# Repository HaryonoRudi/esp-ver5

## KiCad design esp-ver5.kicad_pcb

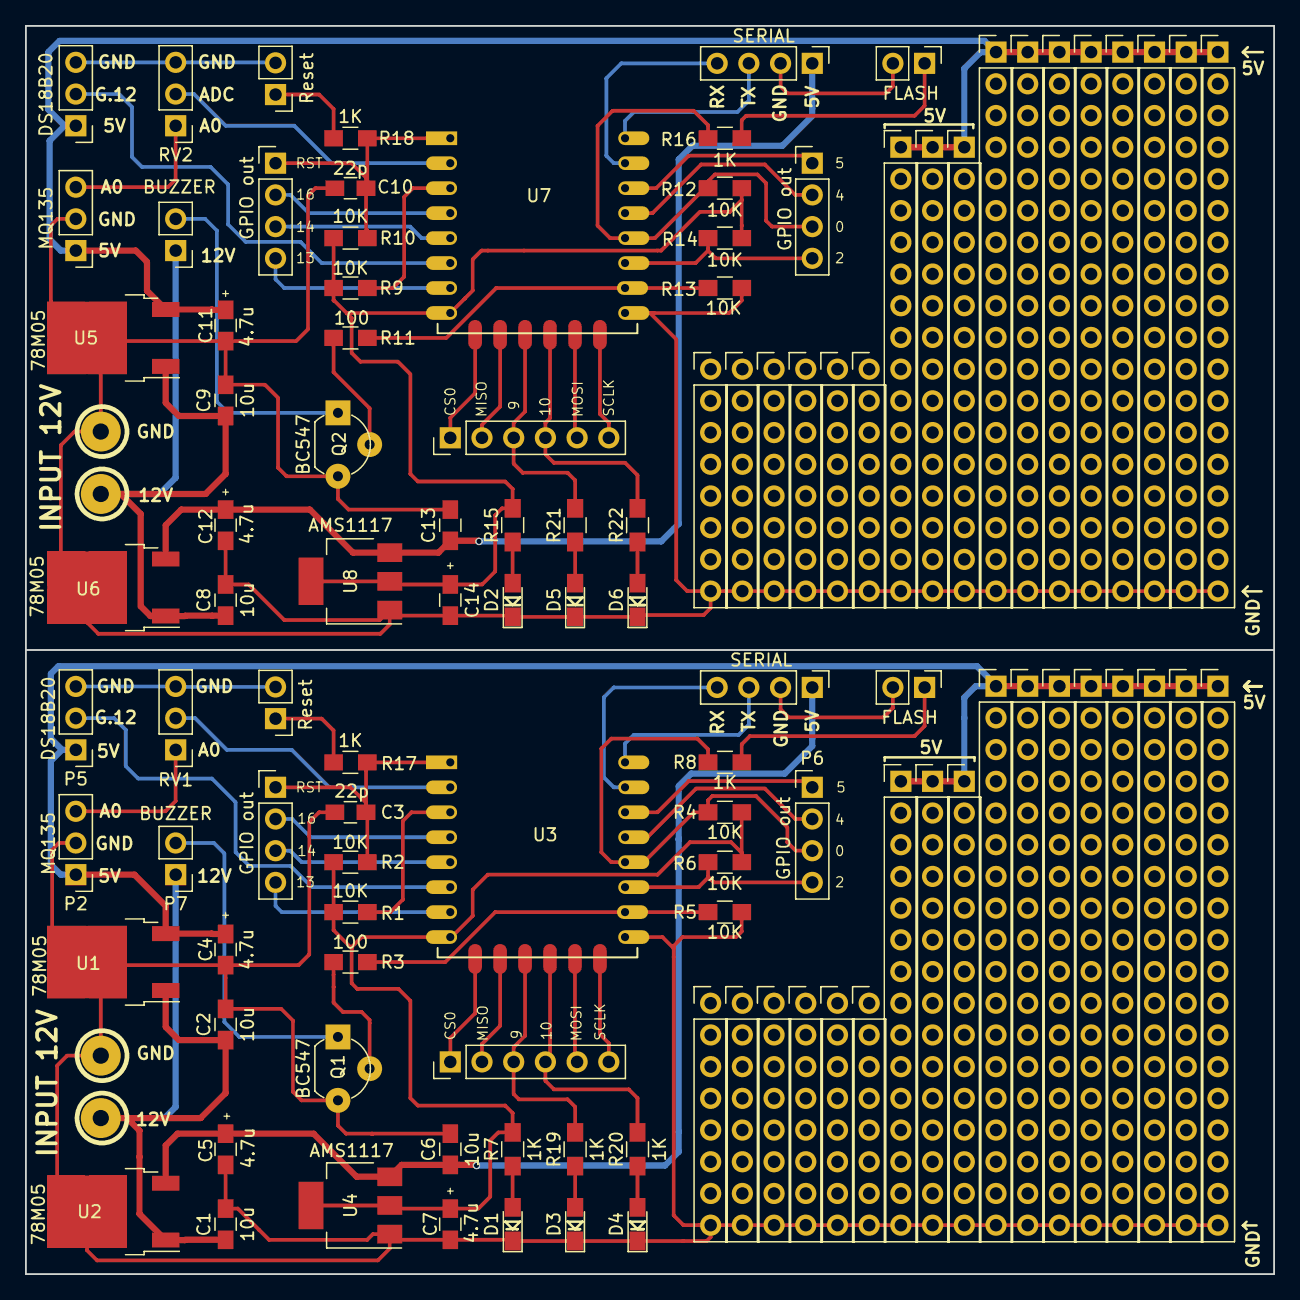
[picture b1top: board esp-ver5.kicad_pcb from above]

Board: 2 copper layers, 100.0 x 100.0 mm, 108 parts (0 on the bottom side), 65 nets.

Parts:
C1, C2, C6, C8, C9, C13: 10u; C_0805_HandSoldering
C3, C10: 22p; C_0805_HandSoldering
C4, C5, C7, C11, C12, C14: 4.7u; C_0805_HandSoldering
D1, D2, D3, D4, D5, D6: LED; LED_0805_HandSoldering
JP1, JP2: FLASH; Pin_Header_Straight_1x02_Pitch2.54mm
JP3, JP4: Reset; Pin_Header_Straight_1x02_Pitch2.54mm
P1, P8: INPUT 12V; mkds_1,5-2
P2, P9: MQ135; Pin_Header_Straight_1x03_Pitch2.54mm
P3, P10: SERIAL; Pin_Header_Straight_1x04_Pitch2.54mm
P4, P6, P13, P14: GPIO out; Pin_Header_Straight_1x04_Pitch2.54mm
P5, P11: DS18B20; Pin_Header_Straight_1x03_Pitch2.54mm
P7, P12: BUZZER; Pin_Header_Straight_1x02_Pitch2.54mm
P15, P16: GPIO out; Pin_Header_Straight_1x06_Pitch2.54mm
P17, P19, P21, P23, P24, P25, P28, P29, P34, P36, P38, P40, P43, P46, P49, P50: P; Pin_Header_Straight_1x18_Pitch2.54mm
P18, P20, P22, P35, P37, P39: P; Pin_Header_Straight_1x15_Pitch2.54mm
P26, P27, P30, P31, P32, P33, P41, P42, P44, P45, P47, P48: P; Pin_Header_Straight_1x08_Pitch2.54mm
Q1, Q2: BC547; TO-92_Molded_Wide
R1, R2, R4, R5, R6, R9, R10, R12, R13, R14: 10K; R_0805_HandSoldering
R3, R11: 100; R_0805_HandSoldering
R7, R8, R15, R16, R17, R18, R19, R20, R21, R22: 1K; R_0805_HandSoldering
RV1, RV2: 10K; Pin_Header_Straight_1x03_Pitch2.54mm
U1, U2, U5, U6: 78M05; TO-252-2
U3, U7: ESP-12E
U4, U8: AMS1117; SOT-223-3Lead_TabPin2

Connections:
3.3v: C14.1, R9.1, R10.2, R12.2, R14.2, R15.2, U7.8, U8.2
3V3: C7.1, R1.1, R2.2, R4.2, R6.2, R7.2, U3.8, U4.2
5.0v: C12.1, C13.1, P10.1, U6.3, U8.3
5V: C5.1, C6.1, P3.1, U2.3, U4.3
12V: C1.1, C2.1, P1.1, P7.1, U1.1, U2.1
A0: P2.3, RV1.1
ADC: RV1.2, U3.2
CS0: P15.1, U3.17
EN: R1.2, U3.3
G0: P14.3, R12.1, R16.1, U7.12
G2: P14.4, R14.1, U7.11
G4: P14.2, U7.13
G5: P14.1, U7.14
G9: P16.3, R21.2, U7.19
G10: P16.4, R22.2, U7.20
G12: P11.2, U7.6
G13: P13.4, U7.7
G14: P13.3, U7.5
G15: R11.2, R13.2, U7.10
G16: P13.2, U7.4
GND: C1.2, C2.2, C3.1, C4.2, C5.2, C6.2, C7.2, C8.2, C9.2, C10.1, C11.2, C12.2, C13.2, C14.2, D1.1, D2.1, D3.1, D4.1, D5.1, D6.1, JP1.2, JP2.2, JP3.2, JP4.2, P1.2, P2.2, P3.2, P5.3, P8.2, P9.2, P10.2, P11.3, P17.18, P18.15, P19.18, P20.15, P21.18, P22.15, P23.18, P24.18, P25.18, P26.8, P27.8, P28.18, P29.18, P30.8, P31.8, P32.8, P33.8, P34.18, P35.15, P36.18, P37.15, P38.18, P39.15, P40.18, P41.8, P42.8, P43.18, P44.8, P45.8, P46.18, P47.8, P48.8, P49.18, P50.18, Q1.3, Q2.3, R5.1, R13.1, RV1.3, RV2.3, U1.2, U2.2, U3.9, U4.1, U5.2, U6.2, U7.9, U8.1
GP0: P6.3, R4.1, R8.1, U3.12
GP2: P6.4, R6.1, U3.11
GP4: P6.2, U3.13
GP5: P6.1, U3.14
GP9: P15.3, R19.2, U3.19
GP10: P15.4, R20.2, U3.20
GP12: P5.2, U3.6
GP13: P4.4, U3.7
GP14: P4.3, U3.5
GP15: R3.2, R5.2, U3.10
GP16: P4.2, U3.4
MISO: P15.2, U3.18
MOSI: P15.5, U3.21
unnamed: D1.2, R7.1
unnamed: D2.2, R15.1
unnamed: D3.2, R19.1
unnamed: D4.2, R20.1
unnamed: D5.2, R21.1
unnamed: D6.2, R22.1
unnamed: JP1.1, R8.2
unnamed: JP2.1, R16.2
unnamed: JP3.1, R17.2
unnamed: JP4.1, R18.2
unnamed: P7.2, Q1.1
unnamed: P12.2, Q2.1
unnamed: Q1.2, R3.1
unnamed: Q2.2, R11.1
RST: C3.2, P4.1, R2.1, R17.1, U3.1
RXD: P3.4, U3.15
SCLK: P15.6, U3.22
TXD: P3.3, U3.16
V5: C4.1, P2.1, P5.1, P17.1, P18.1, P19.1, P20.1, P21.1, P22.1, P23.1, P24.1, P25.1, P28.1, P29.1, U1.3
V5.0: C11.1, P9.1, P11.1, P34.1, P35.1, P36.1, P37.1, P38.1, P39.1, P40.1, P43.1, P46.1, P49.1, P50.1, U5.3
V12: C8.1, C9.1, P8.1, P12.1, U5.1, U6.1
a01: P9.3, RV2.1
adc1: RV2.2, U7.2
cs: P16.1, U7.17
en_ch: R9.2, U7.3
miso1: P16.2, U7.18
mosi1: P16.5, U7.21
reset: C10.2, P13.1, R10.1, R18.1, U7.1
rx: P10.4, U7.15
sclk1: P16.6, U7.22
tx: P10.3, U7.16

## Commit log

2017-09-06 ESP VER5 Finished
